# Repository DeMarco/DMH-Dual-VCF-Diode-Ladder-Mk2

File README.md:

# DMH-Dual-VCF-Diode-Ladder-Mk2
Version 2 of my dual Diode Ladder VCF module

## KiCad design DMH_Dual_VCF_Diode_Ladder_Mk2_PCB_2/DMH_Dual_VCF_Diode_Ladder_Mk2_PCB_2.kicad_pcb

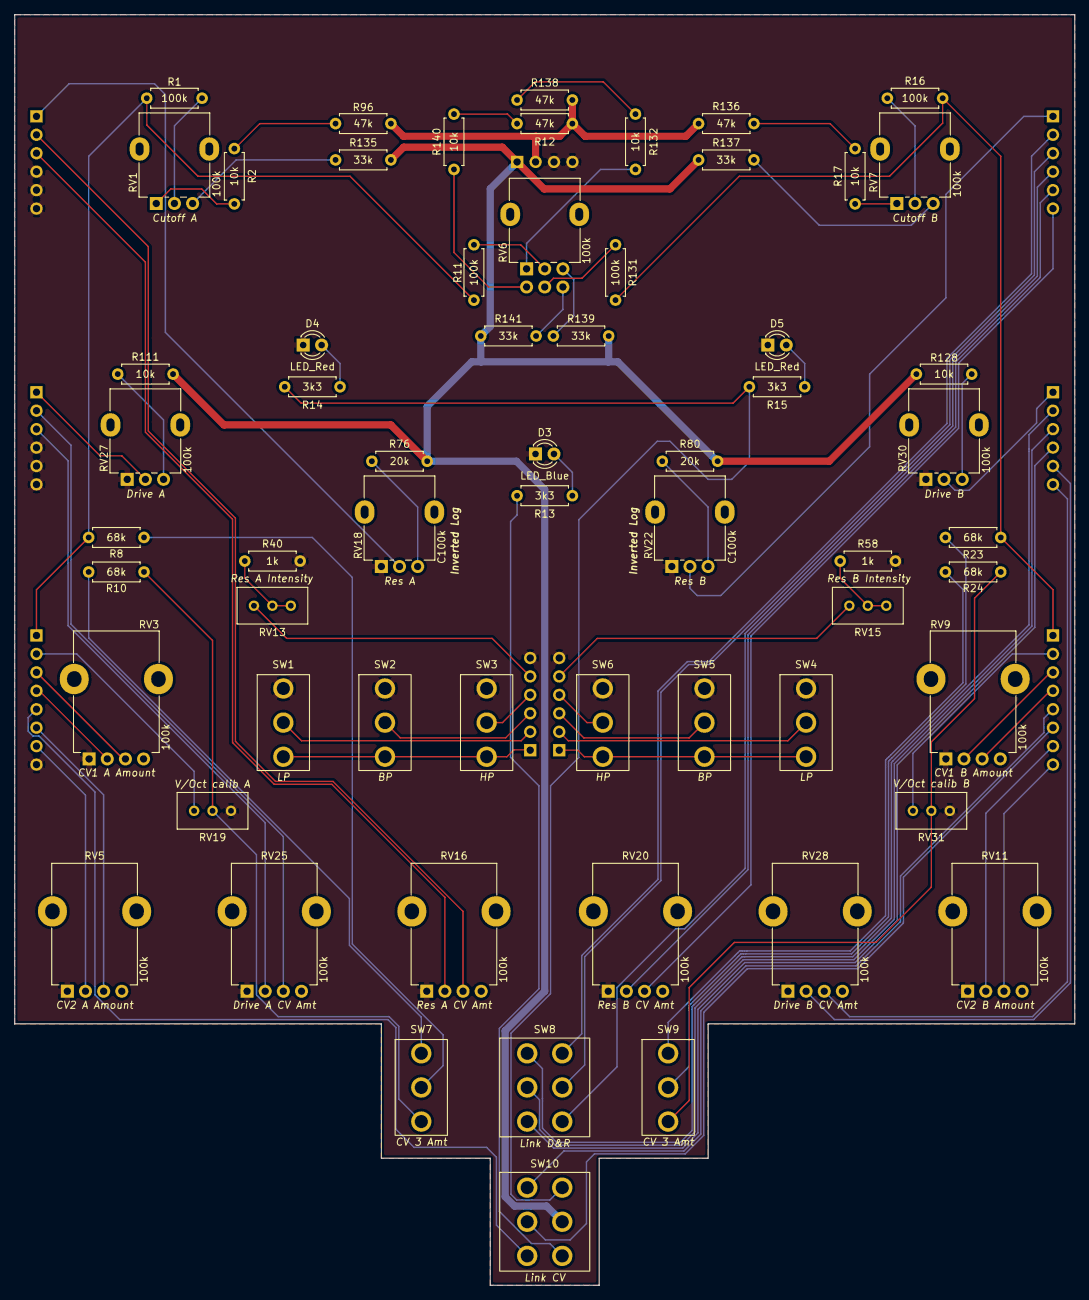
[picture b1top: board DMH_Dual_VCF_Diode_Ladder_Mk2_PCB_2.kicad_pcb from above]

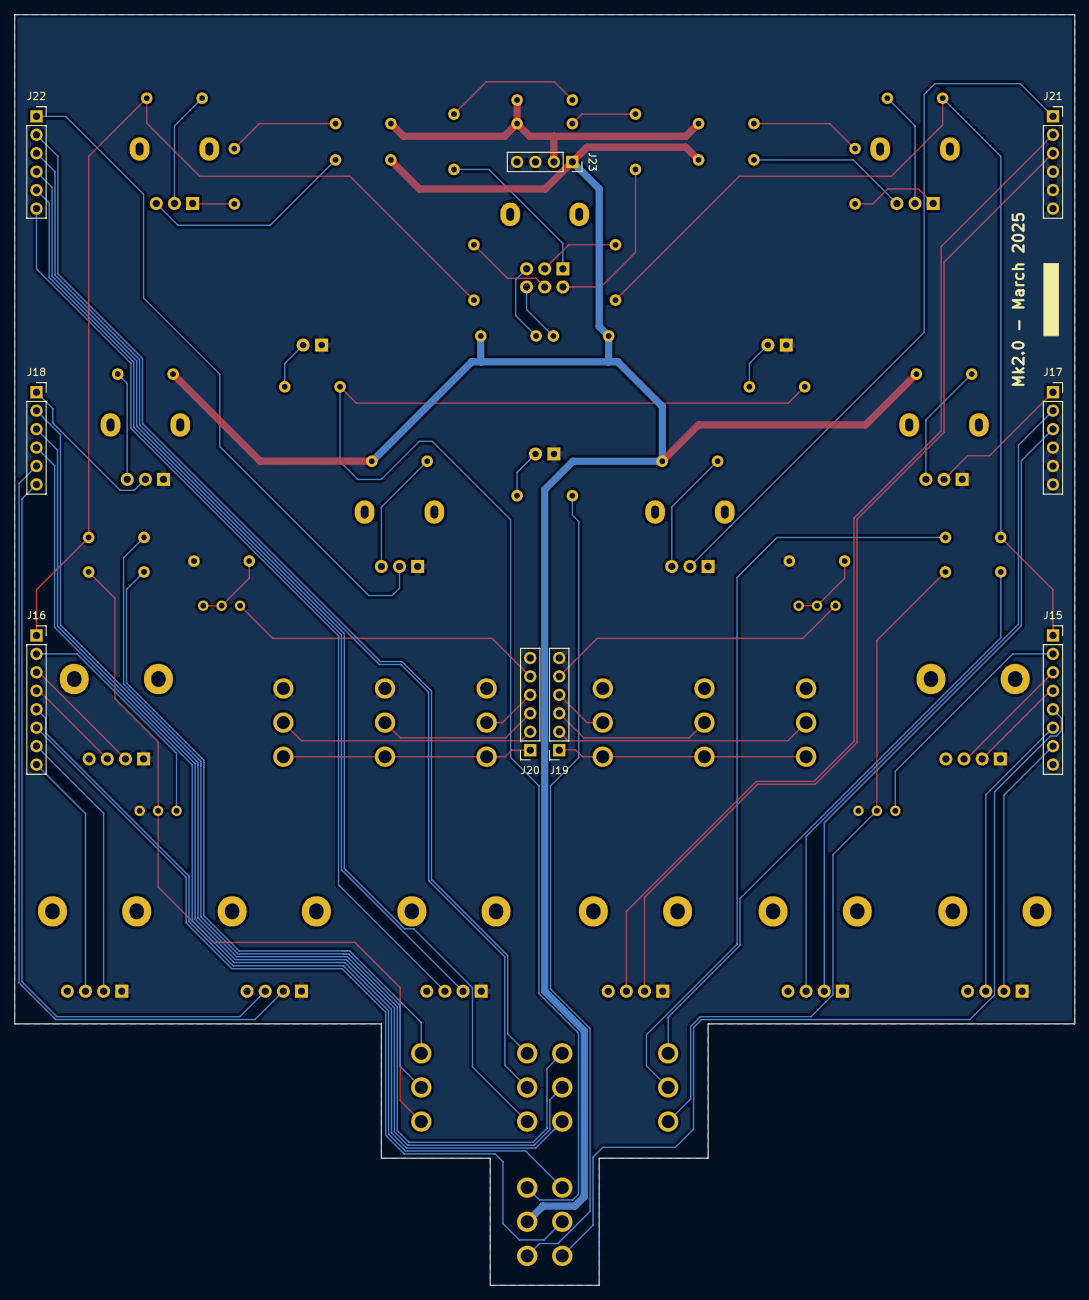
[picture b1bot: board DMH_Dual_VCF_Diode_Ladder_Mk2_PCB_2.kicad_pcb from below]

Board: 2 copper layers, 146.0 x 175.0 mm, 70 parts (9 on the bottom side), 79 nets.

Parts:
D3: LED_Blue; LED_D3.0mm
D4, D5: LED_Red; LED_D3.0mm
J15, J16: Conn_01x08_PinHeader; PinSocket_1x08_P2.54mm_Vertical
J17, J18, J19, J20, J21, J22: Conn_01x06_PinHeader; PinSocket_1x06_P2.54mm_Vertical
J23: Conn_01x04_PinHeader; PinSocket_1x04_P2.54mm_Vertical
R1, R11, R16, R131: 100k; R_Axial_DIN0207_L6.3mm_D2.5mm_P7.62mm_Horizontal
R2, R17, R111, R128, R132, R140: 10k; R_Axial_DIN0207_L6.3mm_D2.5mm_P7.62mm_Horizontal
R8, R10, R23, R24: 68k; R_Axial_DIN0207_L6.3mm_D2.5mm_P7.62mm_Horizontal
R12, R96, R136, R138: 47k; R_Axial_DIN0207_L6.3mm_D2.5mm_P7.62mm_Horizontal
R13, R14, R15: 3k3; R_Axial_DIN0207_L6.3mm_D2.5mm_P7.62mm_Horizontal
R40, R58: 1k; R_Axial_DIN0207_L6.3mm_D2.5mm_P7.62mm_Horizontal
R76, R80: 20k; R_Axial_DIN0207_L6.3mm_D2.5mm_P7.62mm_Horizontal
R135, R137, R139, R141: 33k; R_Axial_DIN0207_L6.3mm_D2.5mm_P7.62mm_Horizontal
RV1, RV7, RV27, RV30: 100k; Potentiometer_Alpha_RD901F-40-00D_Single_Vertical
RV3, RV5, RV9, RV11, RV16, RV20, RV25, RV28: 100k; Potentiometer_TT_P110KH1
RV6: 100k; Potentiometer_Alpha_RD902F-40-00D_Dual_Vertical
RV13, RV15: 50k; Potentiometer_Bourns_3296W_Vertical
RV18, RV22: C100k; Potentiometer_Alpha_RD901F-40-00D_Single_Vertical
RV19, RV31: 100k; Potentiometer_Bourns_3296W_Vertical
SW1, SW2, SW3, SW4, SW5, SW6: SW_SPDT; Toggle_Switch_TE
SW7, SW9: SW_SPDT_OnOffOn; Toggle_Switch_TE
SW8: SW_DPDT_x2; Toggle_Switch_2_Poles_TE
SW10: SW_DPDT_OnOn; Toggle_Switch_2_Poles_TE

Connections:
+12V: J23.1, R76.2, R80.2, R111.2, R128.2, R135.2, R137.1, R139.2, R141.1, SW10.5 (B)
-12V: J23.2, R12.2, R96.1, R136.1, R138.2
/CV Processing/CV1 A Input: J15.3, RV3.3
/CV Processing/CV1 B Input: J16.4, RV9.3
/CV Processing/CV2 A Input: J15.6, RV5.3
/CV Processing/CV2 B Input: J16.8, RV11.3
/CV Processing/CV A: J15.5, SW10.1 (A)
/CV Processing/CV B: J16.5, SW10.3 (C)
/CV Processing/Link CV Switch: J16.6, SW10.2 (B)
/Drive A/Drive CV: J18.4, SW8.1 (A)
/Drive A/Drive CV Input: J17.2, RV25.3
/Drive B/Drive CV Input: J18.6, RV28.3
/Inputs and Outputs A/Res CV Jack: J21.2, RV16.3
/Inputs and Outputs B/Res CV Jack: J22.6, RV20.3
/Resonance A CV/Res CV: J22.4, SW8.4 (A)
GND: D3.1 (K), D4.1 (K), D5.1 (K), J15.8, J17.4, J17.5, J17.6, J19.6, J20.6, J21.4, J21.5, J21.6, J23.3, J23.4, R40.2, R58.2, RV3.1, RV5.1, RV9.1, RV11.1, RV16.1, RV18.1, RV19.3, RV20.1, RV22.1, RV25.1, RV27.1, RV28.1, RV30.1, RV31.3, SW1.3 (C), SW2.3 (C), SW3.3 (C), SW4.3 (C), SW5.3 (C), SW6.3 (C)
unnamed: D3.2 (A), R13.2
unnamed: D4.2 (A), R14.2
unnamed: D5.2 (A), R15.2
unnamed: J15.1, R1.2, R8.1, R11.2
unnamed: J15.2, RV19.1
unnamed: J15.4, RV3.2
unnamed: J15.7, RV5.2
unnamed: J16.1, R16.2, R23.1, R131.2
unnamed: J16.2, RV31.1
unnamed: J16.3, RV9.2
unnamed: J16.7, RV11.2
unnamed: J17.1, RV27.2
unnamed: J17.3, RV25.2
unnamed: J18.1, RV30.2
unnamed: J18.2, SW8.3 (C)
unnamed: J18.3, SW8.2 (B)
unnamed: J18.5, RV28.2
unnamed: J19.1, SW1.1 (A), SW2.1 (A), SW3.1 (A)
unnamed: J19.2, SW1.2 (B)
unnamed: J19.3, SW2.2 (B)
unnamed: J19.4, SW3.2 (B)
unnamed: J19.5, RV13.1
unnamed: J20.1, SW4.1 (A), SW5.1 (A), SW6.1 (A)
unnamed: J20.2, SW4.2 (B)
unnamed: J20.3, SW5.2 (B)
unnamed: J20.4, SW6.2 (B)
unnamed: J20.5, RV15.1
unnamed: J21.1, RV18.2
unnamed: J21.3, RV16.2
unnamed: J22.1, RV22.2
unnamed: J22.2, SW8.6 (C)
unnamed: J22.3, SW8.5 (B)
unnamed: J22.5, RV20.2
unnamed: R1.1, RV1.2
unnamed: R2.1, RV1.1
unnamed: R2.2, R96.2
unnamed: R11.1, RV6.2
unnamed: R12.1, R140.2
unnamed: R13.1, SW10.4 (A)
unnamed: R14.1, R15.1, SW10.6 (C)
unnamed: R16.1, RV7.2
unnamed: R17.1, RV7.1
unnamed: R40.1, RV13.2, RV13.3
unnamed: R58.1, RV15.2, RV15.3
unnamed: R76.1, RV18.3
unnamed: R80.1, RV22.3
unnamed: R111.1, RV27.3
unnamed: R128.1, RV30.3
unnamed: R131.1, RV6.5
unnamed: R132.1, RV6.1
unnamed: R132.2, R138.1
unnamed: R135.1, RV1.3
unnamed: R17.2, R136.2
unnamed: R137.2, RV7.3
unnamed: R139.1, RV6.3
unnamed: R140.1, RV6.4
unnamed: R141.2, RV6.6
unnamed: R10.2, RV19.2, SW7.1 (A)
unnamed: R8.2, SW7.2 (B)
unnamed: R10.1, SW7.3 (C)
unnamed: R24.2, RV31.2, SW9.1 (A)
unnamed: R23.2, SW9.2 (B)
unnamed: R24.1, SW9.3 (C)

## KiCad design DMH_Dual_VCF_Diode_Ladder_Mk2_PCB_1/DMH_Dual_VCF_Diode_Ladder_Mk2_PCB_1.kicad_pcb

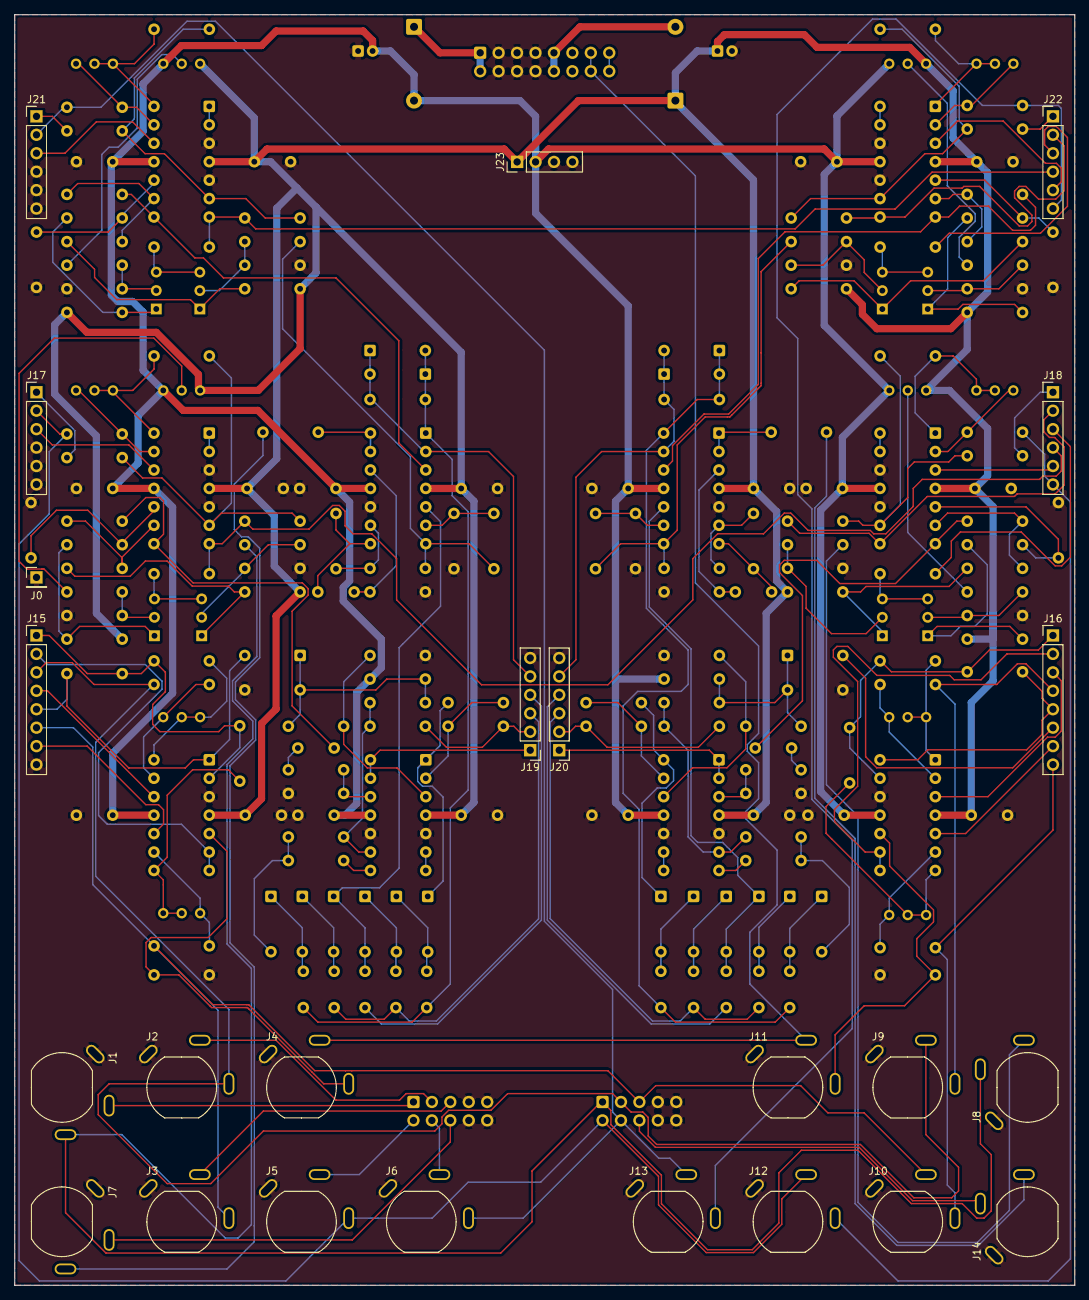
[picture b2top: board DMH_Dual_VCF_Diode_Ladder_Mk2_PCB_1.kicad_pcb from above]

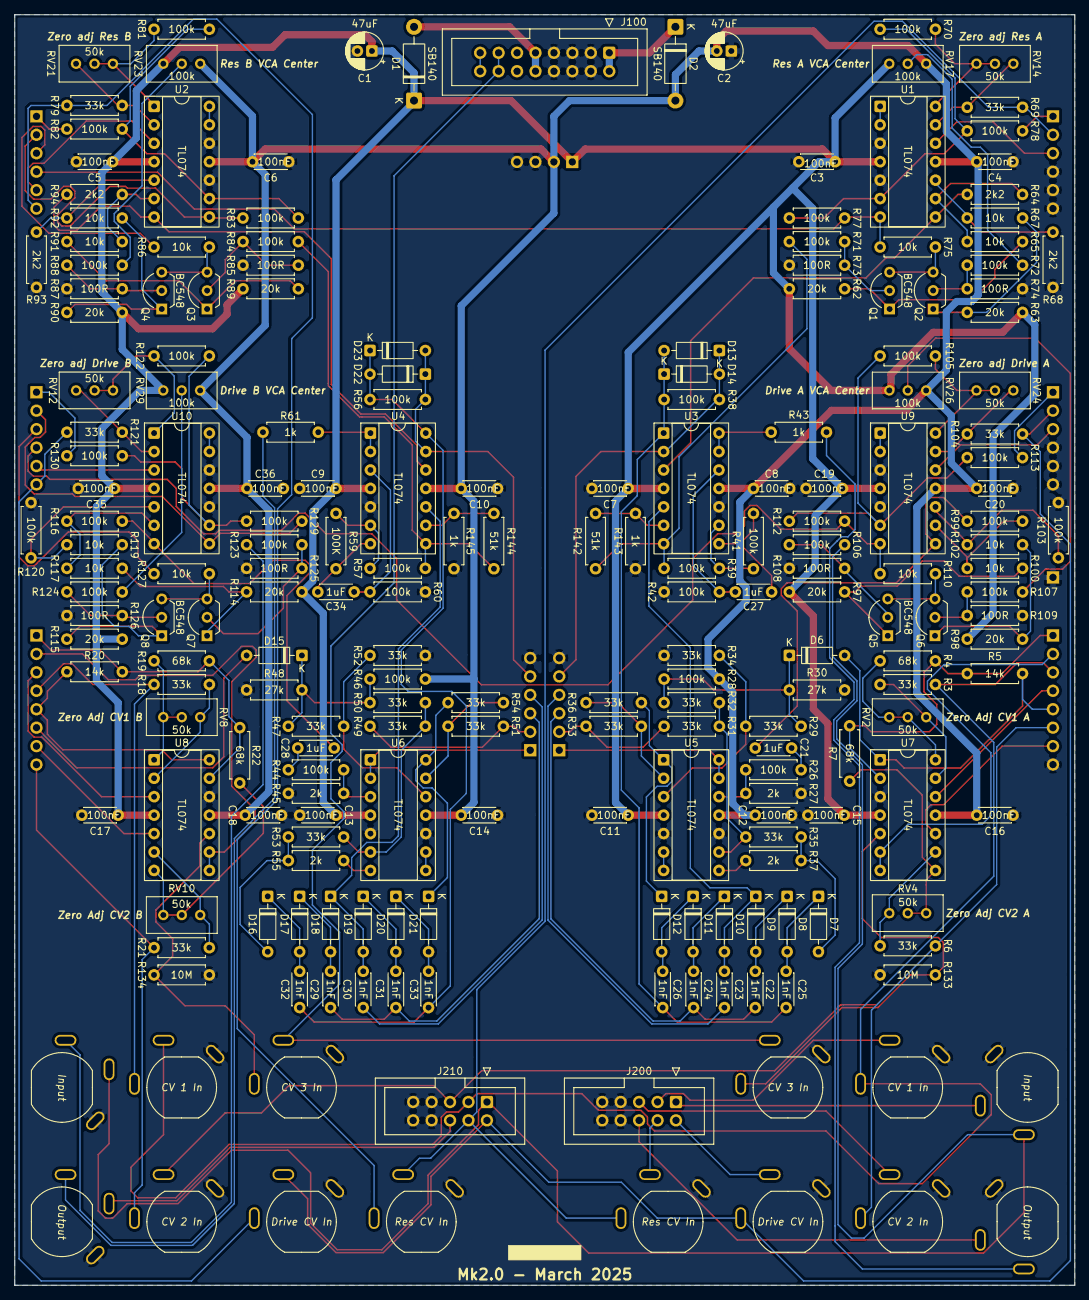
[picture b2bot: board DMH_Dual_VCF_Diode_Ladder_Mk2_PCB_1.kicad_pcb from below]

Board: 2 copper layers, 146.0 x 175.0 mm, 223 parts (199 on the bottom side), 167 nets.

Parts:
C1, C2: 47uF; CP_Radial_D5.0mm_P2.00mm
C3, C4, C5, C6, C7, C8, C9, C10, C11, C12, C13, C14, C15, C16, C17, C18, C19, C20, C35, C36: 100nF; C_Disc_D4.3mm_W1.9mm_P5.00mm
C21, C27, C28, C34: 1uF; C_Disc_D4.3mm_W1.9mm_P5.00mm
C22, C23, C24, C25, C26, C29, C30, C31, C32, C33: 1nF; C_Disc_D4.3mm_W1.9mm_P5.00mm
D1, D2: SB140; D_DO-41_SOD81_P10.16mm_Horizontal
D6, D7, D8, D9, D10, D11, D12, D13, D14, D15, D16, D17, D18, D19, D20, D21, D22, D23: 1N4148; D_DO-35_SOD27_P7.62mm_Horizontal
J0: Conn_01x01; PinHeader_1x01_P2.54mm_Vertical
J1, J2, J3, J4, J5, J6, J7, J8, J9, J10, J11, J12, J13, J14: TS_Jack_6.35mm_Sw; CUI_MJ-63052A
J15, J16: Conn_01x08_PinHeader; PinHeader_1x08_P2.54mm_Vertical
J17, J18, J19, J20, J21, J22: Conn_01x06_PinHeader; PinHeader_1x06_P2.54mm_Vertical
J23: Conn_01x04_PinHeader; PinHeader_1x04_P2.54mm_Vertical
J100: IDC_02x08; IDC-Header_2x08_P2.54mm_Vertical_Eurorack
J200, J210: IDC_02x05; IDC-Header_2x05_P2.54mm_Vertical_BackBone
Q1, Q2, Q3, Q4, Q5, Q6, Q7, Q8: BC548; TO-92L_Inline_Wide
R3, R6, R18, R21, R29, R31, R32, R33, R34, R35, R36, R47, R49, R50, R51, R52, R53, R54, R69, R79, R104, R121: 33k; R_Axial_DIN0207_L6.3mm_D2.5mm_P7.62mm_Horizontal
R4, R7, R19, R22: 68k; R_Axial_DIN0207_L6.3mm_D2.5mm_P7.62mm_Horizontal
R5, R20: 14k; R_Axial_DIN0207_L6.3mm_D2.5mm_P7.62mm_Horizontal
R26, R28, R38, R39, R41, R42, R44, R46, R56, R57, R60, R70, R71, R72, R77, R78, R81, R82, R83, R84, R88, R99, R103, R105, R106, R107, R112, R113, R116, R120, R122, R123, R124, R129, R130: 100k; R_Axial_DIN0207_L6.3mm_D2.5mm_P7.62mm_Horizontal
R27, R37, R45, R55: 2k; R_Axial_DIN0207_L6.3mm_D2.5mm_P7.62mm_Horizontal
R30, R48: 27k; R_Axial_DIN0207_L6.3mm_D2.5mm_P7.62mm_Horizontal
R43, R61, R143, R145: 1k; R_Axial_DIN0207_L6.3mm_D2.5mm_P7.62mm_Horizontal
R59: 100K; R_Axial_DIN0207_L6.3mm_D2.5mm_P7.62mm_Horizontal
R62, R63, R89, R90, R97, R98, R114, R115: 20k; R_Axial_DIN0207_L6.3mm_D2.5mm_P7.62mm_Horizontal
R64, R68, R93, R94: 2k2; R_Axial_DIN0207_L6.3mm_D2.5mm_P7.62mm_Horizontal
R65, R67, R75, R86, R91, R92, R100, R102, R110, R117, R119, R127: 10k; R_Axial_DIN0207_L6.3mm_D2.5mm_P7.62mm_Horizontal
R73, R74, R85, R87, R108, R109, R125, R126: 100R; R_Axial_DIN0207_L6.3mm_D2.5mm_P7.62mm_Horizontal
R133, R134: 10M; R_Axial_DIN0207_L6.3mm_D2.5mm_P7.62mm_Horizontal
R142, R144: 51k; R_Axial_DIN0207_L6.3mm_D2.5mm_P7.62mm_Horizontal
RV2, RV4, RV8, RV10, RV12, RV14, RV21, RV24: 50k; Potentiometer_Bourns_3296W_Vertical
RV17, RV23, RV26, RV29: 100k; Potentiometer_Bourns_3296W_Vertical
U1, U2, U3, U4, U5, U6, U7, U8, U9, U10: TL074; DIP-14_W7.62mm_Socket

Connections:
+12V: C1.1, C3.1, C5.1, C7.1, C9.1, C11.1, C13.1, C15.1, C17.1, C19.1, C35.1, D1.1 (K), J23.1, R62.2, R63.2, R89.2, R90.2, R97.2, R98.2, R114.2, R115.2, RV17.3, RV23.3, RV26.3, RV29.3, U1.4 (V+), U2.4 (V+), U3.4 (V+), U4.4 (V+), U5.4 (V+), U6.4 (V+), U7.4 (V+), U8.4 (V+), U9.4 (V+), U10.4 (V+)
-12V: C2.2, C4.2, C6.2, C8.2, C10.2, C12.2, C14.2, C16.2, C18.2, C20.2, C36.2, D2.2 (A), J23.2, R28.1, R46.1, RV17.1, RV23.1, RV26.1, RV29.1, U1.11 (V-), U2.11 (V-), U3.11 (V-), U4.11 (V-), U5.11 (V-), U6.11 (V-), U7.11 (V-), U8.11 (V-), U9.11 (V-), U10.11 (V-)
/CV Processing/CV1 A Input: J2.T, J9.TN, J15.3, J210.2, R3.1
/CV Processing/CV1 B Input: J9.T, J16.4, R18.1
/CV Processing/CV2 A Input: J3.T, J10.TN, J15.6, J210.3, R6.1
/CV Processing/CV2 B Input: J10.T, J16.8, R21.1
/CV Processing/CV3 A Input: J4.T, R133.2, U7.5 (+)
/CV Processing/CV3 B Input: J11.T, R134.2, U8.10 (+)
/CV Processing/CV A: D6.2 (A), J15.5, R5.2, U7.1
/CV Processing/CV B: J16.5, R20.2, U8.14
/CV Processing/Link CV Switch: D15.2 (A), J16.6
/Core Circuit A/Input: C21.1, R99.1, U9.8
/Core Circuit A/Output: J7.T, R43.2
/Core Circuit A/Raw Output: R39.1, R71.2, R142.2, U3.7
/Core Circuit A/Res Input: R64.1, U1.8, U3.3 (+)
/Core Circuit B/Input: C28.1, R116.1, U10.7
/Core Circuit B/Output: J14.T, R61.2
/Core Circuit B/Raw Output: R57.1, R84.2, R144.2, U4.8
/Core Circuit B/Res Input: R94.1, U2.7, U4.12 (+)
/Drive A/Drive CV: J18.4, R110.1, R112.2, U9.7
/Drive A/Drive CV Input: J5.T, J12.TN, J17.2, J210.6, R104.1
/Drive A/Input: J1.T, J8.TN, J210.1, R106.2
/Drive B/Drive CV Input: J12.T, J18.6, R121.1
/Drive B/Input: J8.T, R123.2
/Inputs and Outputs A/CV 3 TN: J4.TN, J11.TN, J100.7a, J100.7b
/Inputs and Outputs A/Res CV Jack: J6.T, J13.TN, J21.2, J210.7, R69.1
/Inputs and Outputs B/Res CV Jack: J13.T, J22.6, R79.1
/Power/Bus Gate: J100.8a, J100.8b
/Resonance A CV/Res CV: J22.4, R75.1, R77.2, U1.7
GND: C1.2, C2.1, C3.2, C4.1, C5.2, C6.1, C7.2, C8.1, C9.2, C10.1, C11.2, C12.1, C13.2, C14.1, C15.2, C16.1, C17.2, C18.1, C19.2, C20.1, C35.2, C36.1, J0.1, J1.S, J2.S, J3.S, J4.S, J5.S, J6.S, J7.S, J8.S, J9.S, J10.S, J11.S, J12.S, J13.S, J14.S, J15.8, J17.4, J17.5, J17.6, J19.6, J20.6, J21.4, J21.5, J21.6, J23.3, J23.4, J100.2a, J100.2b, J100.3a, J100.3b, J100.4a, J100.4b, J200.4, J200.5, J200.9, J200.10, J210.4, J210.5, J210.9, J210.10, R27.1, R30.2, R34.1, R42.1, R45.1, R48.2, R52.1, R60.1, R68.2, R73.1, R74.1, R85.1, R87.1, R93.2, R103.2, R108.1, R109.1, R120.2, R125.1, R126.1, R133.1, R134.1, R143.1, R145.1, U1.3 (+), U1.5 (+), U2.10 (+), U2.12 (+), U3.10 (+), U4.5 (+), U5.5 (+), U5.10 (+), U6.5 (+), U6.10 (+), U7.3 (+), U8.12 (+), U9.3 (+), U9.5 (+), U10.10 (+), U10.12 (+)
unnamed: C21.2, R26.1
unnamed: C27.1, R41.2, U3.8
unnamed: C28.2, R44.1
unnamed: C34.1, R59.2, U4.7
unnamed: D1.2 (A), J100.5a, J100.5b
unnamed: D2.1 (K), J100.1a, J100.1b
unnamed: D6.1 (K), R28.2, R29.1, R30.1, R32.1
unnamed: D7.2 (A), R35.2, R37.2
unnamed: C25.1, D7.1 (K), D8.2 (A)
unnamed: C22.2, D8.1 (K), D9.2 (A)
unnamed: C23.2, D9.1 (K), D10.2 (A), U3.5 (+)
unnamed: C24.2, D10.1 (K), D11.2 (A)
unnamed: C26.1, D11.1 (K), D12.2 (A)
unnamed: D12.1 (K), R36.2, U5.1
unnamed: C25.2, C26.2, D13.2 (A), D14.1 (K), R38.1, U3.1
unnamed: D13.1 (K), D14.2 (A), J19.5, R38.2, U3.2 (-)
unnamed: D15.1 (K), R46.2, R47.1, R48.1, R50.1
unnamed: D16.2 (A), R53.2, R55.2
unnamed: C32.1, D16.1 (K), D17.2 (A)
unnamed: C29.2, D17.1 (K), D18.2 (A)
unnamed: C30.2, D18.1 (K), D19.2 (A), U4.10 (+)
unnamed: C31.2, D19.1 (K), D20.2 (A)
unnamed: C33.1, D20.1 (K), D21.2 (A)
unnamed: D21.1 (K), R54.2, U6.14
unnamed: C32.2, C33.2, D22.2 (A), D23.1 (K), R56.1, U4.14
unnamed: D22.1 (K), D23.2 (A), J20.5, R56.2, U4.13 (-)
unnamed: J15.1, R4.2, R5.1, R7.2, U7.2 (-)
unnamed: J15.2, U7.6 (-), U7.7
unnamed: J15.4, U7.12 (+)
unnamed: J15.7, U7.10 (+)
unnamed: J16.1, R19.2, R20.1, R22.2, U8.13 (-)
unnamed: J16.2, U8.8, U8.9 (-)
unnamed: J16.3, U8.3 (+)
unnamed: J16.7, U8.5 (+)
unnamed: J17.1, R113.1
unnamed: J17.3, U9.12 (+)
unnamed: J18.1, R130.1
unnamed: J18.2, R129.2, U10.8
unnamed: J18.3, R127.1
unnamed: J18.5, U10.3 (+)
unnamed: J19.1, U5.13 (-), U5.14
unnamed: J19.2, R31.1, R33.1
unnamed: C22.1, C24.1, J19.3
unnamed: C23.1, J19.4
unnamed: J20.1, U6.1, U6.2 (-)
unnamed: J20.2, R49.1, R51.1
unnamed: C29.1, C31.1, J20.3
unnamed: C30.1, J20.4
unnamed: J21.1, R78.1
unnamed: J21.3, U1.12 (+)
unnamed: J22.1, R82.1
unnamed: J22.2, R83.2, U2.8
unnamed: J22.3, R86.1
unnamed: J22.5, U2.3 (+)
unnamed: J1.TN, J200.1
unnamed: J2.TN, J200.2
unnamed: J3.TN, J200.3
unnamed: J5.TN, J200.6
unnamed: J6.TN, J200.7
unnamed: J7.TN, J200.8
unnamed: J14.TN, J210.8
unnamed: Q1.2 (B), R71.1, R73.2
unnamed: Q1.1 (C), R62.1, R65.2
unnamed: Q1.3 (E), Q2.3 (E), R75.2
unnamed: Q2.2 (B), R72.2, R74.2
unnamed: Q2.1 (C), R63.1, R67.2
unnamed: Q3.2 (B), R84.1, R85.2
unnamed: Q3.1 (C), R89.1, R91.2
unnamed: Q3.3 (E), Q4.3 (E), R86.2
unnamed: Q4.2 (B), R87.2, R88.2
unnamed: Q4.1 (C), R90.1, R92.2
unnamed: Q5.2 (B), R106.1, R108.2
unnamed: Q5.1 (C), R97.1, R100.2
unnamed: Q5.3 (E), Q6.3 (E), R110.2
unnamed: Q6.2 (B), R107.2, R109.2
unnamed: Q6.1 (C), R98.1, R102.2
unnamed: Q7.2 (B), R123.1, R125.2
unnamed: Q7.1 (C), R114.1, R117.2
unnamed: Q7.3 (E), Q8.3 (E), R127.2
unnamed: Q8.2 (B), R124.2, R126.2
unnamed: Q8.1 (C), R115.1, R119.2
unnamed: R4.1, RV2.2, RV2.3, U7.14
unnamed: R7.1, RV4.2, RV4.3, U7.8
unnamed: R19.1, RV8.2, RV8.3, U8.1
unnamed: R22.1, RV10.2, RV10.3, U8.7
unnamed: R37.1, U5.8
unnamed: R55.1, U6.7
unnamed: R70.1, RV14.2, RV14.3, U1.14
unnamed: R72.1, RV17.2
unnamed: R81.1, RV21.2, RV21.3, U2.1
unnamed: R88.1, RV23.2
unnamed: R105.1, RV24.2, RV24.3, U9.14
unnamed: R107.1, RV26.2
unnamed: R122.1, RV12.2, RV12.3, U10.1
unnamed: R124.1, RV29.2
unnamed: U1.1, U1.2 (-)
unnamed: R70.2, R77.1, R78.2, U1.6 (-)
unnamed: R67.1, R68.1, U1.10 (+)
unnamed: R64.2, R65.1, U1.9 (-)
unnamed: R69.2, RV14.1, U1.13 (-)
unnamed: R79.2, RV21.1, U2.2 (-)
unnamed: R92.1, R93.1, U2.5 (+)
unnamed: R91.1, R94.2, U2.6 (-)
unnamed: R81.2, R82.2, R83.1, U2.9 (-)
unnamed: U2.13 (-), U2.14
unnamed: R142.1, R143.2, U3.6 (-)
unnamed: R39.2, R41.1, U3.9 (-)
unnamed: C27.2, R42.2, U3.12 (+)
unnamed: R43.1, U3.13 (-), U3.14
unnamed: C34.2, R60.2, U4.3 (+)
unnamed: R61.1, U4.1, U4.2 (-)
unnamed: R57.2, R59.1, U4.6 (-)
unnamed: R144.1, R145.2, U4.9 (-)
unnamed: R29.2, R34.2, U5.3 (+)
unnamed: R33.2, R36.1, U5.2 (-)
unnamed: U5.6 (-), U5.7
unnamed: R31.2, R32.2, R35.1, U5.9 (-)
unnamed: R26.2, R27.2, U5.12 (+)
unnamed: R44.2, R45.2, U6.3 (+)
unnamed: R49.2, R50.2, R53.1, U6.6 (-)
unnamed: U6.8, U6.9 (-)
unnamed: R47.2, R52.2, U6.12 (+)
unnamed: R51.2, R54.1, U6.13 (-)
unnamed: R6.2, RV4.1, U7.9 (-)
unnamed: R3.2, RV2.1, U7.13 (-)
unnamed: R18.2, RV8.1, U8.2 (-)
unnamed: R21.2, RV10.1, U8.6 (-)
unnamed: U9.1, U9.2 (-)
unnamed: R105.2, R112.1, R113.2, U9.6 (-)
unnamed: R102.1, R103.1, U9.10 (+)
unnamed: R99.2, R100.1, U9.9 (-)
unnamed: R104.2, RV24.1, U9.13 (-)
unnamed: R121.2, RV12.1, U10.2 (-)
unnamed: R119.1, R120.1, U10.5 (+)
unnamed: R116.2, R117.1, U10.6 (-)
unnamed: R122.2, R129.1, R130.2, U10.9 (-)
unnamed: U10.13 (-), U10.14

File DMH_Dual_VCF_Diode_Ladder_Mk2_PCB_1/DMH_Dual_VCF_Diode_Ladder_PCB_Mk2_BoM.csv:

Reference,Value,Footprint,Qty
"C1,C2",47uF,Capacitor_THT:CP_Radial_D5.0mm_P2.00mm,2
"C3,C4,C5,C6,C7,C8,C9,C10,C11,C12,C13,C14,C15,C16,C17,C18,C19,C20,C35,C36",100nF,Capacitor_THT:C_Disc_D4.3mm_W1.9mm_P5.00mm,20
"C21,C27,C28,C34",1uF,Capacitor_THT:C_Disc_D4.3mm_W1.9mm_P5.00mm,4
"C22,C23,C24,C25,C26,C29,C30,C31,C32,C33",1nF,Capacitor_THT:C_Disc_D4.3mm_W1.9mm_P5.00mm,10
D1,SB140+,Diode_THT:D_DO-41_SOD81_P10.16mm_Horizontal,1
D2,SB140-,Diode_THT:D_DO-41_SOD81_P10.16mm_Horizontal,1
D3,LED_Blue,LED_THT:LED_D3.0mm,1
"D4,D5",LED_Red,LED_THT:LED_D3.0mm,2
"D6,D7,D8,D9,D10,D11,D12,D13,D14,D15,D16,D17,D18,D19,D20,D21,D22,D23",1N4148,Diode_THT:D_DO-35_SOD27_P7.62mm_Horizontal,18
"J1,J2,J3,J4,J5,J6,J7,J8,J9,J10,J11,J12,J13,J14",TS_Jack_6.35mm_Sw,SynthStuff:CUI_MJ-63052A,14
"J15,J16",Conn_01x08_PinHeader,Connector_PinHeader_2.54mm:PinHeader_1x08_P2.54mm_Vertical,2
"J17,J18,J19,J20,J21,J22",Conn_01x06_PinHeader,Connector_PinHeader_2.54mm:PinHeader_1x06_P2.54mm_Vertical,6
J23,Conn_01x04_PinHeader,Connector_PinHeader_2.54mm:PinHeader_1x04_P2.54mm_Vertical,1
J100,IDC_02x08,SynthStuff:IDC-Header_2x08_P2.54mm_Vertical_Eurorack,1
"J200,J210",IDC_02x05,SynthStuff:IDC-Header_2x05_P2.54mm_Vertical_BackBone,2
"Q1,Q2,Q3,Q4,Q5,Q6,Q7,Q8",BC548,Package_TO_SOT_THT:TO-92L_Inline_Wide,8
"R1,R11,R16,R26,R28,R38,R39,R41,R42,R44,R46,R56,R57,R60,R70,R71,R72,R77,R78,R81,R82,R83,R84,R88,R99,R103,R105,R106,R107,R112,R113,R116,R120,R122,R123,R124,R129,R130,R131",100k,Resistor_THT:R_Axial_DIN0207_L6.3mm_D2.5mm_P7.62mm_Horizontal,39
"R2,R17,R65,R67,R75,R86,R91,R92,R100,R102,R110,R111,R117,R119,R127,R128,R132,R140",10k,Resistor_THT:R_Axial_DIN0207_L6.3mm_D2.5mm_P7.62mm_Horizontal,18
"R3,R6,R18,R21,R29,R31,R32,R33,R34,R35,R36,R47,R49,R50,R51,R52,R53,R54,R69,R79,R104,R121,R135,R137,R139,R141",33k,Resistor_THT:R_Axial_DIN0207_L6.3mm_D2.5mm_P7.62mm_Horizontal,26
"R4,R7,R8,R10,R19,R22,R23,R24",68k,Resistor_THT:R_Axial_DIN0207_L6.3mm_D2.5mm_P7.62mm_Horizontal,8
"R5,R20",14k,Resistor_THT:R_Axial_DIN0207_L6.3mm_D2.5mm_P7.62mm_Horizontal,2
"R12,R96,R136,R138",47k,Resistor_THT:R_Axial_DIN0207_L6.3mm_D2.5mm_P7.62mm_Horizontal,4
"R13,R14,R15",3k3,Resistor_THT:R_Axial_DIN0207_L6.3mm_D2.5mm_P7.62mm_Horizontal,3
"R27,R37,R45,R55",2k,Resistor_THT:R_Axial_DIN0207_L6.3mm_D2.5mm_P7.62mm_Horizontal,4
"R30,R48",27k,Resistor_THT:R_Axial_DIN0207_L6.3mm_D2.5mm_P7.62mm_Horizontal,2
"R40,R43,R58,R61,R143,R145",1k,Resistor_THT:R_Axial_DIN0207_L6.3mm_D2.5mm_P7.62mm_Horizontal,6
R59,100K,Resistor_THT:R_Axial_DIN0207_L6.3mm_D2.5mm_P7.62mm_Horizontal,1
"R62,R63,R76,R80,R89,R90,R97,R98,R114,R115",20k,Resistor_THT:R_Axial_DIN0207_L6.3mm_D2.5mm_P7.62mm_Horizontal,10
"R64,R68,R93,R94",2k2,Resistor_THT:R_Axial_DIN0207_L6.3mm_D2.5mm_P7.62mm_Horizontal,4
"R73,R74,R85,R87,R108,R109,R125,R126",100R,Resistor_THT:R_Axial_DIN0207_L6.3mm_D2.5mm_P7.62mm_Horizontal,8
"R133,R134",10M,Resistor_THT:R_Axial_DIN0207_L6.3mm_D2.5mm_P7.62mm_Horizontal,2
"R142,R144",51k,Resistor_THT:R_Axial_DIN0207_L6.3mm_D2.5mm_P7.62mm_Horizontal,2
"RV1,RV7,RV18,RV22,RV27,RV30",100k,SynthStuff:Potentiometer_Alpha_RD901F-40-00D_Single_Vertical,6
"RV2,RV4,RV8,RV10,RV12,RV13,RV14,RV15,RV21,RV24",50k,Potentiometer_THT:Potentiometer_Bourns_3296W_Vertical,10
"RV3,RV5,RV9,RV11,RV16,RV20,RV25,RV28",100k,SynthStuff:Potentiometer_TT_P110KH1,8
RV6,100k,Potentiometer_THT:Potentiometer_Alpha_RD902F-40-00D_Dual_Vertical,1
"RV17,RV23,RV26,RV29",100k,Potentiometer_THT:Potentiometer_Bourns_3296W_Vertical,4
"RV19,RV31",100k,,2
"SW1,SW2,SW3,SW4,SW5,SW6",SW_SPDT,SynthStuff:Toggle_Switch_TE,6
"SW7,SW9",SW_SPDT_OnOffOn,SynthStuff:Toggle_Switch_TE,2
SW8,SW_DPDT_x2,SynthStuff:Toggle_Switch_2_Poles_TE,1
SW10,SW_DPDT_OnOn,SynthStuff:Toggle_Switch_2_Poles_TE,1
"U1,U2,U3,U4,U5,U6,U7,U8,U9,U10",TL074,Package_DIP:DIP-14_W7.62mm_Socket,10

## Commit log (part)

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2025-01-14 Created KiCad projects
2025-01-15 Added CV3 and Drive CV to Panel
2025-01-15 Added CV3 and Drive CV to I/O pages
2025-01-18 Added board-to-board pins to schematic
2025-01-19 Created Drive CV circuits
2025-01-19 Added inter-board pins to all circuits
2025-01-20 Connecting main blocks in progress
2025-01-20 Connected all hierarchical pins
2025-01-21 Annotating OpAmps in progress
2025-01-21 Reannotated OpAmps and cleared errors
2025-01-22 Set Exclude From Board properties for main PCB
2025-01-22 Corrected pin header footprint assignments
2025-01-22 Created pots PCB project
2025-01-22 Exclude From Board in progress
2025-01-22 Complete Exclude From Board on PCB 2
2025-01-22 Component placement on PCB2 in progress
2025-01-23 pcb 2 routing in progress
2025-01-24 Finished PCB 2
2025-01-25 Replaced Central Cutoff pot with dual port
2025-01-26 PCB1 component placement in progress
2025-02-17 Routed one half
2025-02-17 Placed components on circuit B
2025-02-17 Routed circuit B
2025-02-18 Added trim pot functions to silkscreen
2025-02-18 Adjusted pin header connections
2025-02-23 Converted to KiCad 9
2025-02-23 Changed VCA CV summing stage feedback to 100k
2025-03-01 Adding buffered input to CV3 - in progress
2025-03-01 Added buffering to each CV 3 input separately
2025-03-01 Added buffer 10M resistors to PCB 1
2025-03-02 validation ongoing
2025-03-03 Updated schematic during validation
    - Changed Resonance B VCA gain resistors to 2k2
    - Added range limiting resistors to all Cutoff pots
    - Moved 48x gain to non-inverting opamp stage in Core Circuit to allow for Resonance voltage control.
2025-03-08 Updated various resistor values
    ... and deleted all VCAs output 1k resistors
2025-03-09 Corrected polarization of dual pot in PCB 1 sch
2025-03-12 Adapted CV3 A Input for V/Oct
    Now need to repeat it for CV3 B
2025-03-14 Added V/oct calib to CV3 B
    And changed output inverter stage resistors back to 100k
2025-03-15 Moved Res Int and CV3 V/Oct trims to front panel
2025-03-15 Synchronized changes from PCB 1 to PCB 2 schematic
2025-03-15 Updated PCB 2 with validated features
2025-03-15 Finished Mk2.0
2025-03-15 Generated Gerbers
2025-03-17 Generated BoM
2025-03-17 Regenerated BoM
2025-03-24 Mistakes found during assembly
2025-05-03 Changed Resonance pots to Taper C type
2025-05-07 Exported BoM
2025-10-03 Updated to Kicad 9
2025-10-08 Updated Kicad 9
2025-11-30 KiCad 9
2026-01-31 KiCad 9.0.7 + centralized library
2026-02-22 Simulated zener limiting
2026-03-31 Update SynthStuff
2026-04-03 Re-exported Gerbers
2026-04-03 Moved zipped Gerbers to root folder
2026-04-03 Renamed schematics PDF
2026-05-23 KiCad 10
